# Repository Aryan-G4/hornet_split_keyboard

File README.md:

# Hornet Keyboard — Split Wireless Communication and Charging Mechanical Keyboard PCB

The Hornet Keyboard is the *first* fully custom, split, mechanical keyboard featuring integrated **Bluetooth**, **Qi wireless charging** on either split, and optional **USB-C programmability/Connectivity**.  
This project represents a complete end-to-end embedded hardware design — from schematic capture to multi-layer PCB layout — optimized for both performance and manufacturability.

---

## Project Overview

| Feature | Description |
|----------|-------------|
| **Form Factor** | Compact Split ergonomic layout key matrix |
| **Microcontroller** | Industry standard NRF52840 QIAA semi-BGA |
| **MCU Interface** | USB-C (DFU bootloader + HID communication) and STLinkV3 SWD |
| **Wireless** | On-board Bluetooth LE trace antenna with matched RF trace and controlled impedance |
| **Power** | Dual power paths: 3.7 V LiPo battery or USB VBUS (5 V) with power switching (USB PRIORITY)|
| **Charging Options** | USB-C Power Delivery (5V @ 1000mA) or Qi wireless charging receiver (5V @ 800mA)|
| **Firmware** | DFU-based update over USB; designed for ZMK and QMK-style firmware structure |
| **Sensors** | On-board voltage monitoring and NTC-based battery temperature protection |
| **Other** | Rotary encoders, Jumpers to probe and enable/disable submodules | standardized M3 mounting holes |
---
## Schematics

## Layout

3D model (ish)

Individual Layers:
L1: FCu

L2: In1

L3: In2

L4: BCu

## System Architecture

The system integrates three major electrical domains:

1. **Digital Domain (nRF52840)**
   - Industry standard MCU with built-in BLE 5.4
   - High-speed interrupt-based matrix scanning and battery management.
   - Dedicated power pin for reading battery charge.

2. **Power Management Domain**
   - Dual-source power path with **ideal diode OR-ing** between USB VBUS and LiPo battery.
   - **Li-Ion charge controller** managing both USB and Qi charge inputs.
   - **Dynamic load sharing** ensures stable operation while charging.
   - **Overcurrent and thermal protection** via FET-based switching and NTC feedback.

3. **Wireless RF Domain**
   - Custom-routed **50 Ω matched trace** for the Bluetooth antenna.
   - π-matching network for impedance tuning based on antenna manufacturer data.
   - Keepout and ground clearance zone designed per RF layout guidelines.

---

## Electrical Design Highlights

- **4-layer PCB** for clean separation of signal, power, and RF planes.
- **Differential USB data routing** (D+ / D–) with 90 Ω differential impedance.
- **Common-mode choke** and ESD suppression on USB-C connector for EMI resilience.
- **Reverse-current blocking MOSFET** for power path control between USB and battery.
- **Qi receiver integration** including rectification, voltage regulation, and charge negotiation.
- **Seamless transition** between wireless power and USB without brownout.

## Tools and Workflow

- **KiCad 8.0** — schematic capture and PCB design  
- **JLCPCB / LCSC** — fabrication and component sourcing  
- **SolidWorks** — mechanical fit and case alignment  
- **ZMK** - Open source repo for wireless split keyboards
- **DFU-util** — firmware flashing over USB-C and SWD through my STLinkV3

---

## Firmware Architecture 
- Utilize USBC's DFU to flash all firmware and STLinkV3 to flash in case of USBC fail
- Implement ZMK- wireless open source keyboard firmware kit for wireless split keyboards
- Implement QMK alternatively, for wired keyboards
- Eventually write my own firmware, optimizing speed and runtime.

---

---

## Gallery and work in progress photos :D

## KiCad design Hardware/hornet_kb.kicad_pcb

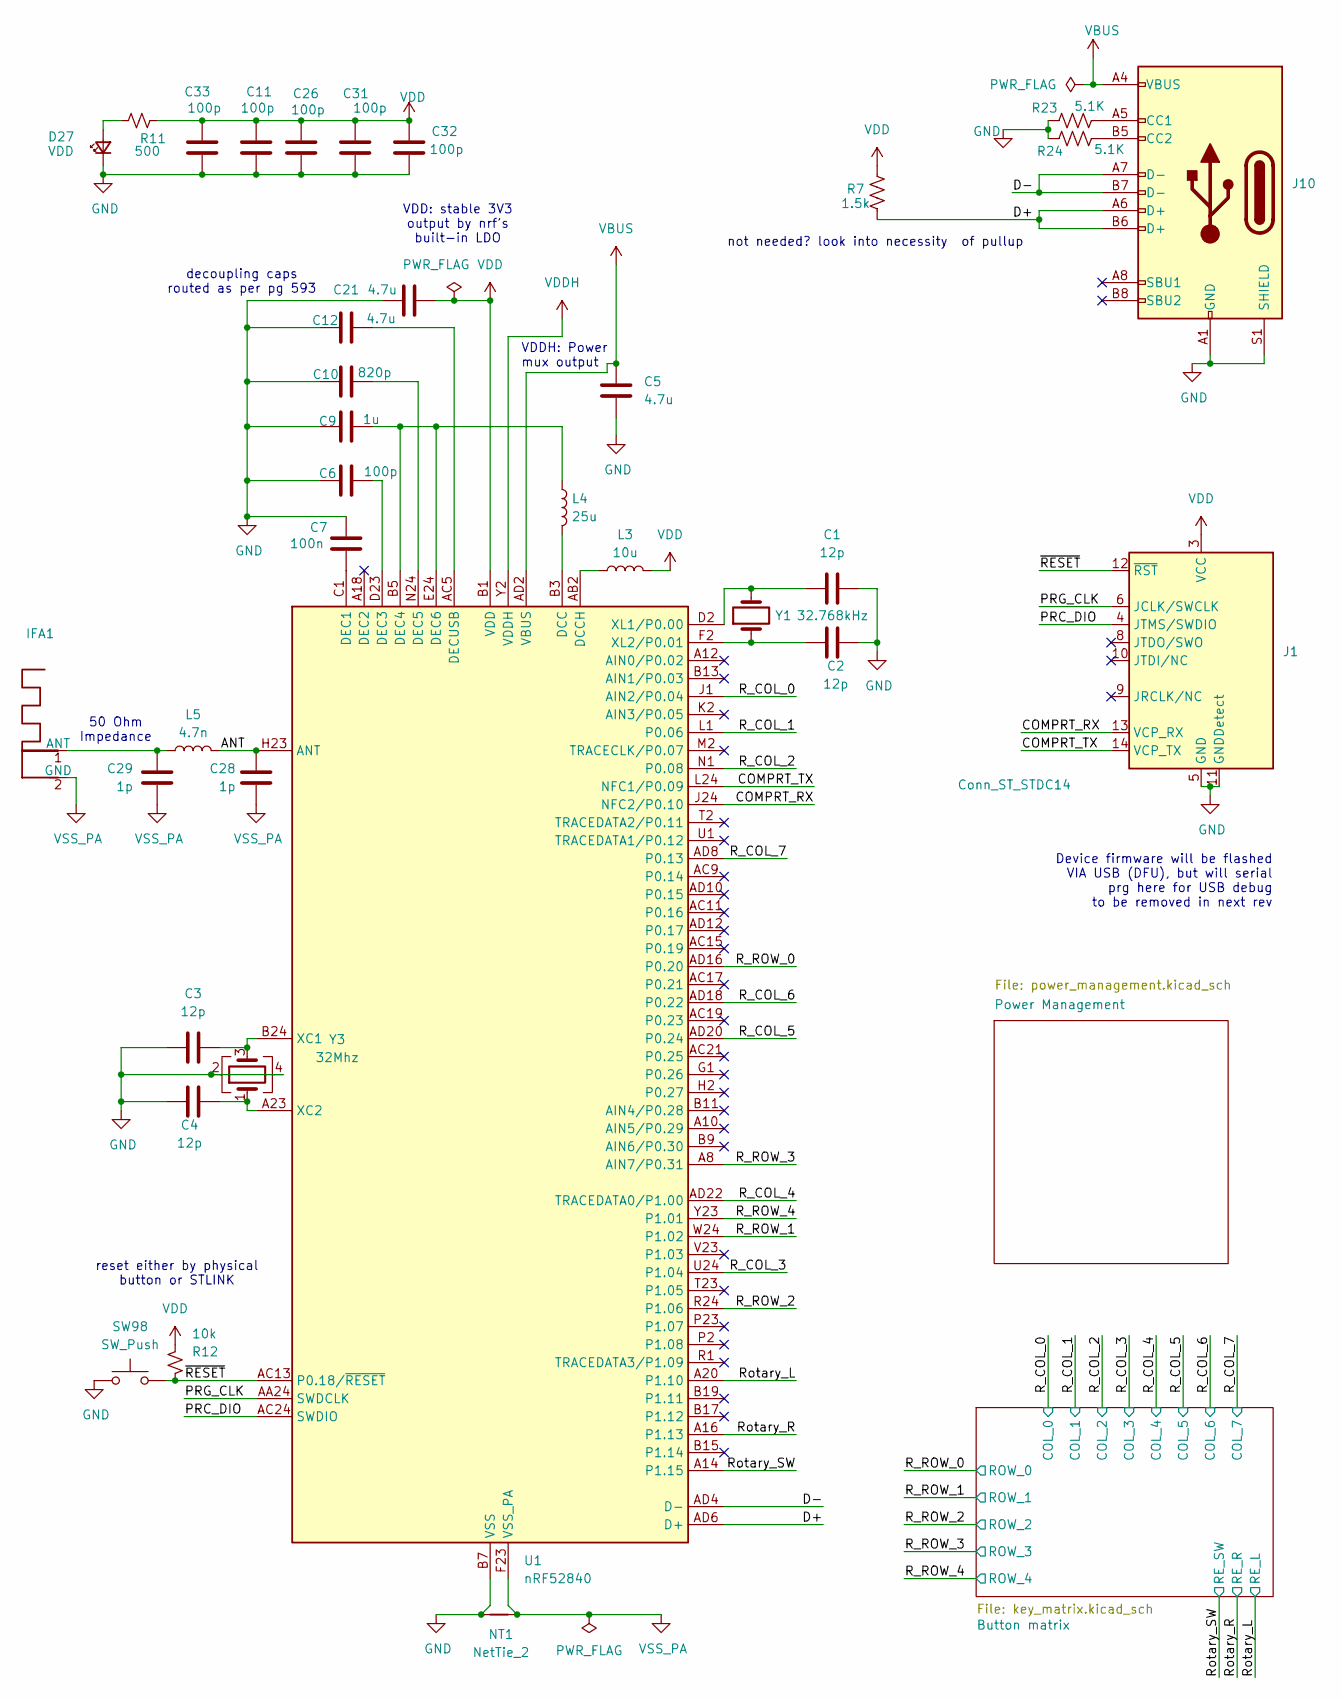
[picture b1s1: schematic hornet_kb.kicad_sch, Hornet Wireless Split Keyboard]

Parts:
C1, C2, C3, C4: 12p; C_0402_1005Metric; LCSC C1547
C5, C12, C21: 4.7u; C_0805_2012Metric; LCSC C1779
C6, C11, C26, C31, C32, C33: 100p; C_0603_1608Metric; LCSC C14858
C7: 100n; C_0603_1608Metric; LCSC C14663
C9: 1u; C_0603_1608Metric; LCSC C15849
C10: 820p; C_0603_1608Metric; LCSC C107057
C28, C29: 1p; C_0402_1005Metric; LCSC C1550
D27: VDD; LED_0402_1005Metric; LCSC C30584803
IFA1: Texas_SWRA117D_2.4GHz_Right
J1: Conn_ST_STDC14; Tag-Connect_TC2070-IDC-FP_2x07_P1.27mm_Vertical
J10: USB_C_Receptacle_USB2.0; USB_C_Receptacle_HRO_TYPE-C-31-M-12; LCSC C165948
L3: 10u; L_0402_1005Metric; LCSC C436512
L4: 25u; L_0402_1005Metric; LCSC C12669
L5: 4.7n; L_0402_1005Metric; LCSC C86065
NT1: NetTie_2; NetTie-2_SMD_Pad2.0mm
R7: 1.5k; R_0603_1608Metric; LCSC C22843
R11: 500; R_0603_1608Metric; LCSC C6207671
R12: 10k; R_0603_1608Metric; LCSC C25804
R23, R24: 5.1K; R_0603_1608Metric; LCSC C23186
SW98: SW_Push; SW_DIP_SPSTx01_Slide_6.7x4.1mm_W6.73mm_P2.54mm_LowProfile_J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; LCSC C720477
U1: nRF52840; Nordic_AQFN-73-1EP_7x7mm_P0.5mm; LCSC C190794
Y1: 32.768kHz; Crystal_SMD_3215-2Pin_3.2x1.5mm; LCSC C32346
Y3: 32Mhz; Crystal_SMD_2016-4Pin_2.0x1.6mm; LCSC C5339095

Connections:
/ANT: C28.1, L5.1, U1.H23 (ANT)
/COMPRT_RX: J1.13 (VCP_RX), U1.J24 (NFC2/P0.10)
/COMPRT_TX: J1.14 (VCP_TX), U1.L24 (NFC1/P0.09)
/D+: J10.A6 (D+), J10.B6 (D+), R7.2, U1.AD6 (D+)
/D-: J10.A7 (D-), J10.B7 (D-), U1.AD4 (D-)
/PRC_DIO: J1.4 (JTMS/SWDIO), U1.AC24 (SWDIO)
/PRG_CLK: J1.6 (JCLK/SWCLK), U1.AA24 (SWDCLK)
/R_COL_0: U1.J1 (AIN2/P0.04); also elsewhere on the board
/R_COL_1: U1.L1 (P0.06); also elsewhere on the board
/R_COL_2: U1.N1 (P0.08); also elsewhere on the board
/R_COL_3: U1.U24 (P1.04); also elsewhere on the board
/R_COL_4: U1.AD22 (TRACEDATA0/P1.00); also elsewhere on the board
/R_COL_5: U1.AD20 (P0.24); also elsewhere on the board
/R_COL_6: U1.AD18 (P0.22); also elsewhere on the board
/R_COL_7: U1.AD8 (P0.13); also elsewhere on the board
/R_ROW_0: U1.AD16 (P0.20); also elsewhere on the board
/R_ROW_1: U1.W24 (P1.02); also elsewhere on the board
/R_ROW_2: U1.R24 (P1.06); also elsewhere on the board
/R_ROW_3: U1.A8 (AIN7/P0.31); also elsewhere on the board
/R_ROW_4: U1.Y23 (P1.01); also elsewhere on the board
/Rotary_L: U1.A20 (P1.10); also elsewhere on the board
/Rotary_R: U1.A16 (P1.13); also elsewhere on the board
/Rotary_SW: U1.A14 (P1.15); also elsewhere on the board
/~RESET: J1.12 (~RST), R12.2, SW98.1, U1.AC13 (P0.18/~RESET)
GND: C1.1, C2.1, C3.1, C4.1, C5.2, C6.2, C7.2, C9.2, C10.1, C11.2, C12.2, C21.1, C26.2, C31.2, C32.2, C33.2, D27.1 (K), J1.5 (GND), J1.7 (GND), J1.11 (GNDDetect), J10.A1 (GND), J10.A12 (GND), J10.B1 (GND), J10.B12 (GND), J10.S1 (SHIELD), NT1.2, R23.1, R24.1, SW98.2, U1.B7 (VSS), U1.EP (VSS), Y3.2, Y3.4; also elsewhere on the board
unnamed: D27.2 (A), R11.2
unnamed: C29.1, IFA1.1 (ANT), L5.2
unnamed: J10.A5 (CC1), R23.2
unnamed: J10.B5 (CC2), R24.2
unnamed: L4.1, U1.B3 (DCC)
unnamed: L3.2, U1.AB2 (DCCH)
unnamed: C7.1, U1.C1 (DEC1)
unnamed: C6.1, U1.D23 (DEC3)
unnamed: C9.1, L4.2, U1.B5 (DEC4), U1.E24 (DEC6)
unnamed: C10.2, U1.N24 (DEC5)
unnamed: C12.1, U1.AC5 (DECUSB)
unnamed: C3.2, U1.B24 (XC1), Y3.3
unnamed: C4.2, U1.A23 (XC2), Y3.1
unnamed: C1.2, U1.D2 (XL1/P0.00), Y1.2
unnamed: C2.2, U1.F2 (XL2/P0.01), Y1.1
VBUS: C5.1, J10.A4 (VBUS), J10.A9 (VBUS), J10.B4 (VBUS), J10.B9 (VBUS), U1.AD2 (VBUS); also elsewhere on the board
VDD: C11.1, C21.2, C26.1, C31.1, C32.1, C33.1, J1.3 (VCC), L3.1, R7.1, R11.1, R12.1, U1.A22 (VDD), U1.AD14 (VDD), U1.AD23 (VDD), U1.B1 (VDD), U1.W1 (VDD); also elsewhere on the board
VDDH: U1.Y2 (VDDH); also elsewhere on the board
VSS_PA: C28.2, C29.2, IFA1.2 (GND), NT1.1, U1.F23 (VSS_PA)

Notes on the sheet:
VDDH: Power mux output
50 Ohm Impedance
Device firmware will be flashed VIA USB (DFU), but will serial prg here for USB debug to be removed in next rev
decoupling caps routed as per pg 593
VDD: stable 3V3 output by nrf's built-in LDO
reset either by physical button or STLINK
not needed? look into necessity of pullup

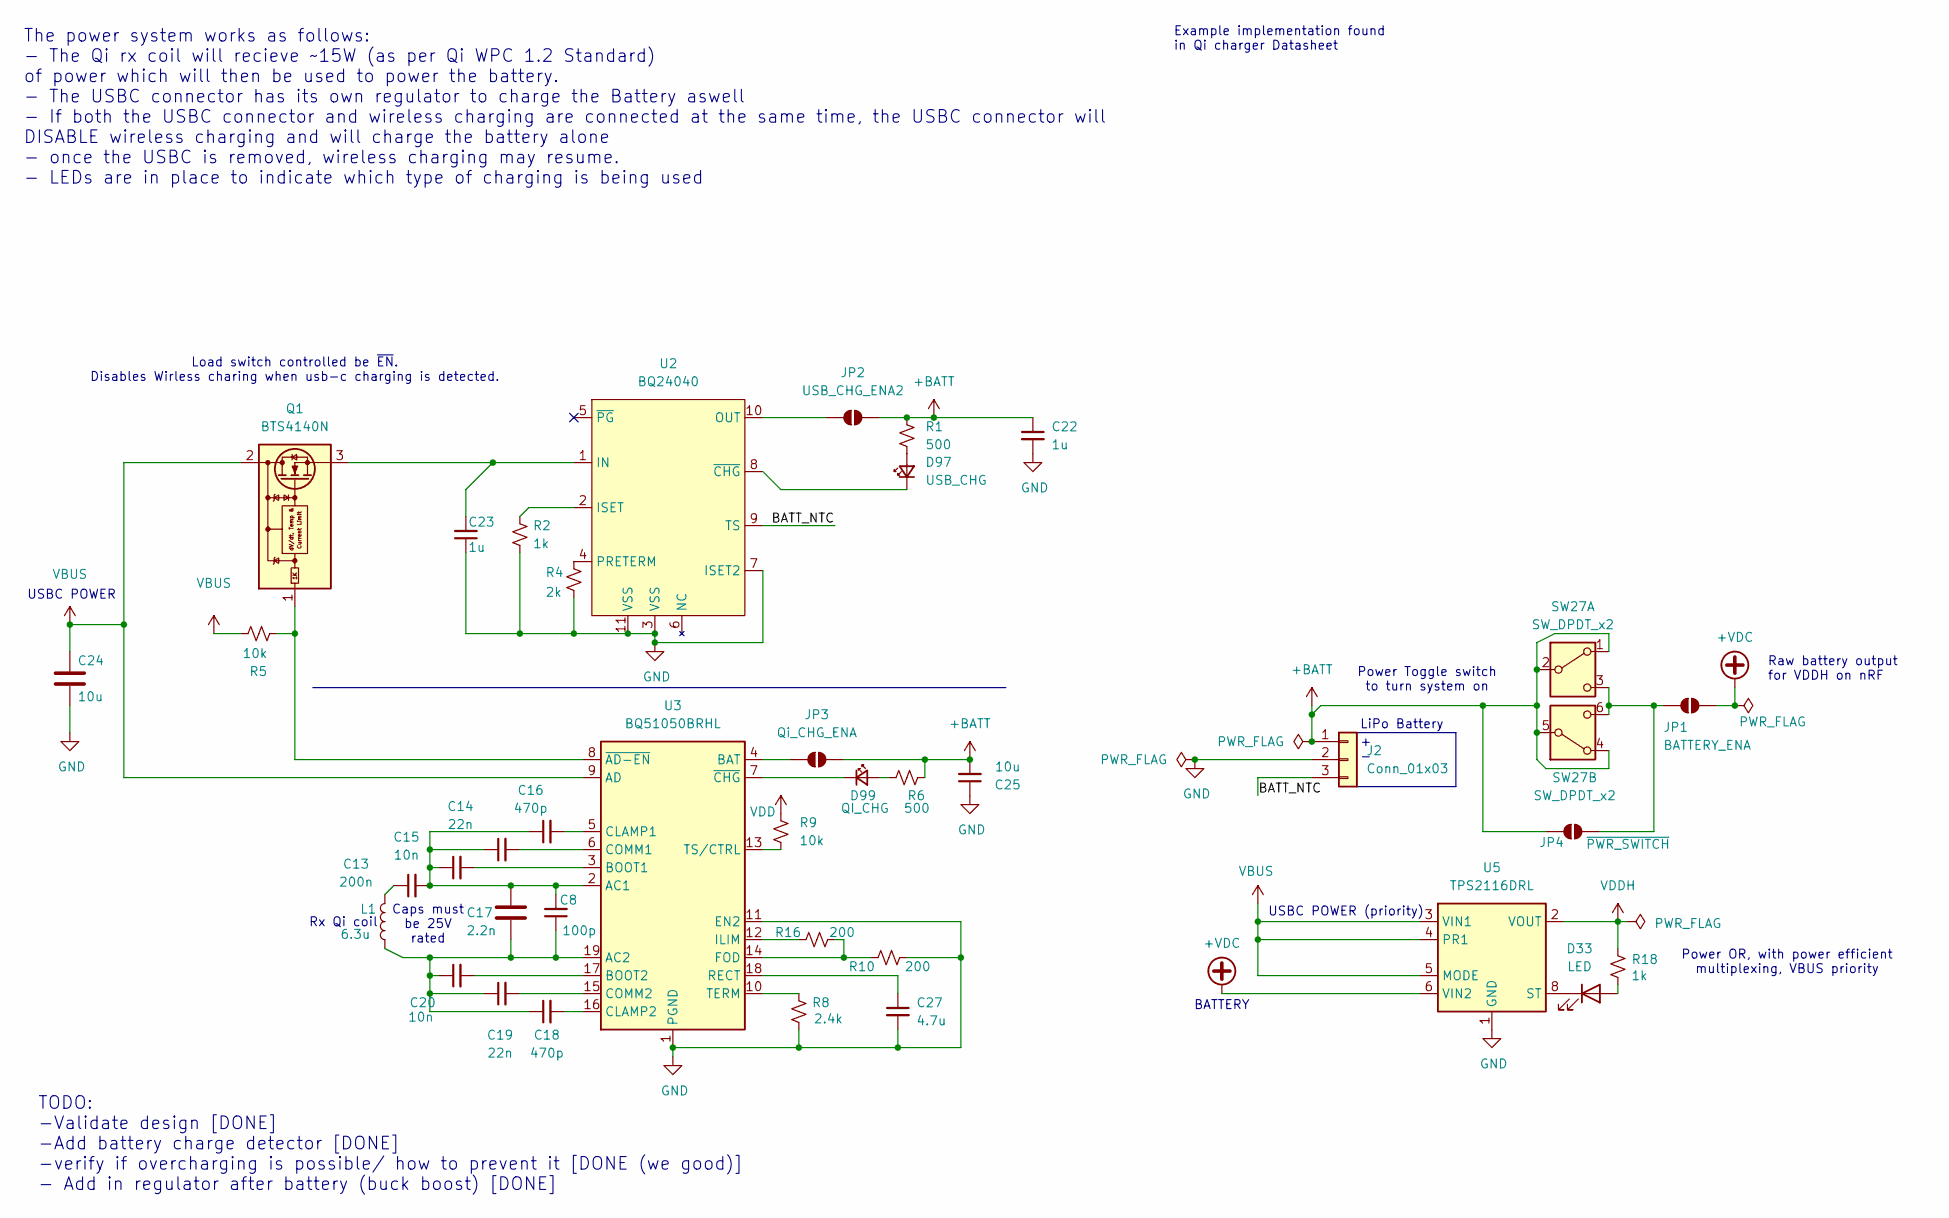
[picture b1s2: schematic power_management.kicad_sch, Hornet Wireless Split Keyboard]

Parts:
C8: 100p; C_0603_1608Metric; LCSC C14858
C13: 200n; C_0603_1608Metric; LCSC C1002
C14, C19: 22n; C_0603_1608Metric; LCSC C21122
C15, C20: 10n; C_0603_1608Metric; LCSC C57112
C16, C18: 470p; C_0603_1608Metric; LCSC C1620
C17: 2.2n; C_0603_1608Metric; LCSC C1604
C22, C23: 1u; C_0603_1608Metric; LCSC C15849
C24, C25: 10u; C_0603_1608Metric; LCSC C19702
C27: 4.7u; C_0603_1608Metric; LCSC C19666
D33: LED; LED_0402_1005Metric; LCSC C28310436
D97: USB_CHG; LED_0402_1005Metric; LCSC C20608784
D99: QI_CHG; LED_0402_1005Metric; LCSC C20608784
J2: Conn_01x03; JST_GH_SM03B-GHS-TB_1x03-1MP_P1.25mm_Horizontal; LCSC C514175
JP1: BATTERY_ENA; SolderJumper-2_P1.3mm_Open_TrianglePad1.0x1.5mm
JP2: USB_CHG_ENA2; SolderJumper-2_P1.3mm_Open_TrianglePad1.0x1.5mm
JP3: Qi_CHG_ENA; SolderJumper-2_P1.3mm_Open_TrianglePad1.0x1.5mm
JP4: ~{PWR_SWITCH}; SolderJumper-2_P1.3mm_Open_TrianglePad1.0x1.5mm
L1: 6.3u; TerminalBlock_Phoenix_MKDS-1,5-2-5.08_1x02_P5.08mm_Horizont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; LCSC C8465
Q1: BTS4140N; SOT-223; LCSC C59442
R1, R6: 500; R_0603_1608Metric; LCSC C6207671
R2, R18: 1k; R_0603_1608Metric; LCSC C21190
R4: 2k; R_0603_1608Metric; LCSC C22975
R5, R9: 10k; R_0603_1608Metric; LCSC C25804
R8: 2.4k; R_0603_1608Metric; LCSC C22940
R10, R16: 200; R_0603_1608Metric; LCSC C8218
SW27: SW_DPDT_x2; SW_CK_JS202011CQN_DPDT_Straight; LCSC C1788494
U2: BQ24040; Texas_DLH0010A_WSON-10-1EP_2.2x2mm_P0.4mm_EP0.9x1.5mm_Therm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; LCSC C2876332
U3: BQ51050BRHL; Texas_VQFN-RHL-20; LCSC C133307
U5: TPS2116DRL; SOT-583-8; LCSC C3235557

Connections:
+BATT: C22.1, C25.2, J2.1, JP2.2 (B), JP3.2 (B), JP4.1 (A), R1.1, R6.1, SW27.1 (A), SW27.2 (B), SW27.4 (A), SW27.5 (B)
+VDC: JP1.2 (B), U5.6 (VIN2)
/Power Management/BATT_NTC: J2.3, U2.9 (TS)
GND: C22.2, C23.1, C24.2, C25.1, C27.2, J2.2, R2.1, R4.1, R8.2, R10.2, U2.3 (VSS), U2.7 (ISET2), U2.11 (VSS), U3.1 (PGND), U3.11 (EN2), U3.20 (PGND), U3.21 (PGND), U5.1 (GND); also elsewhere on the board
unnamed: C13.1, L1.2
unnamed: D33.2 (A), R18.1
unnamed: D33.1 (K), U5.8 (ST)
unnamed: D97.2 (A), R1.2
unnamed: D97.1 (K), U2.8 (~CHG)
unnamed: D99.2 (A), R6.2
unnamed: D99.1 (K), U3.7 (~CHG)
unnamed: JP1.1 (A), JP4.2 (B), SW27.3 (C), SW27.6 (C)
unnamed: JP2.1 (A), U2.10 (OUT)
unnamed: JP3.1 (A), U3.4 (BAT)
unnamed: Q1.1 (IN), R5.1, U3.8 (~AD-EN)
unnamed: C23.2, Q1.3 (OUT), U2.1 (IN)
unnamed: R2.2, U2.2 (ISET)
unnamed: R4.2, U2.4 (PRETERM)
unnamed: C8.2, C13.2, C14.1, C15.1, C16.1, C17.1, U3.2 (AC1)
unnamed: C8.1, C17.2, C18.1, C19.1, C20.1, L1.1, U3.19 (AC2)
unnamed: C15.2, U3.3 (BOOT1)
unnamed: C20.2, U3.17 (BOOT2)
unnamed: C16.2, U3.5 (CLAMP1)
unnamed: C18.2, U3.16 (CLAMP2)
unnamed: C14.2, U3.6 (COMM1)
unnamed: C19.2, U3.15 (COMM2)
unnamed: R10.1, R16.2, U3.14 (FOD)
unnamed: R16.1, U3.12 (ILIM)
unnamed: C27.1, U3.18 (RECT)
unnamed: R8.1, U3.10 (TERM)
unnamed: R9.2, U3.13 (TS/CTRL)
VBUS: C24.1, Q1.2 (V_{bb}), Q1.4 (V_{bb}), R5.2, U3.9 (AD), U5.3 (VIN1), U5.4 (PR1), U5.5 (MODE); also elsewhere on the board
VDD: R9.1; also elsewhere on the board
VDDH: R18.2, U5.2 (VOUT), U5.7 (VOUT); also elsewhere on the board

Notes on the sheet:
Power OR, with power efficient multiplexing, VBUS priority
Rx Qi coil
The power system works as follows: - The Qi rx coil will recieve ~15W (as per Qi WPC 1.2 Standard) of power which will then be used to power the battery. - The USBC connector has its own regulator to charge the Battery aswell - If both the USBC connector and wireless charging are connected at the s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
Raw battery output for VDDH on nRF
USBC POWER (priority)
USBC POWER
LiPo Battery
Example implementation found in Qi charger Datasheet
BATTERY
Caps must be 25V rated
Load switch controlled be ~{EN}. Disables Wirless charing when usb-c charging is detected.
Power Toggle switch to turn system on
+ -
TODO: -Validate design [DONE] -Add battery charge detector [DONE] -verify if overcharging is possible/ how to prevent it [DONE (we good)] - Add in regulator after battery (buck boost) [DONE]

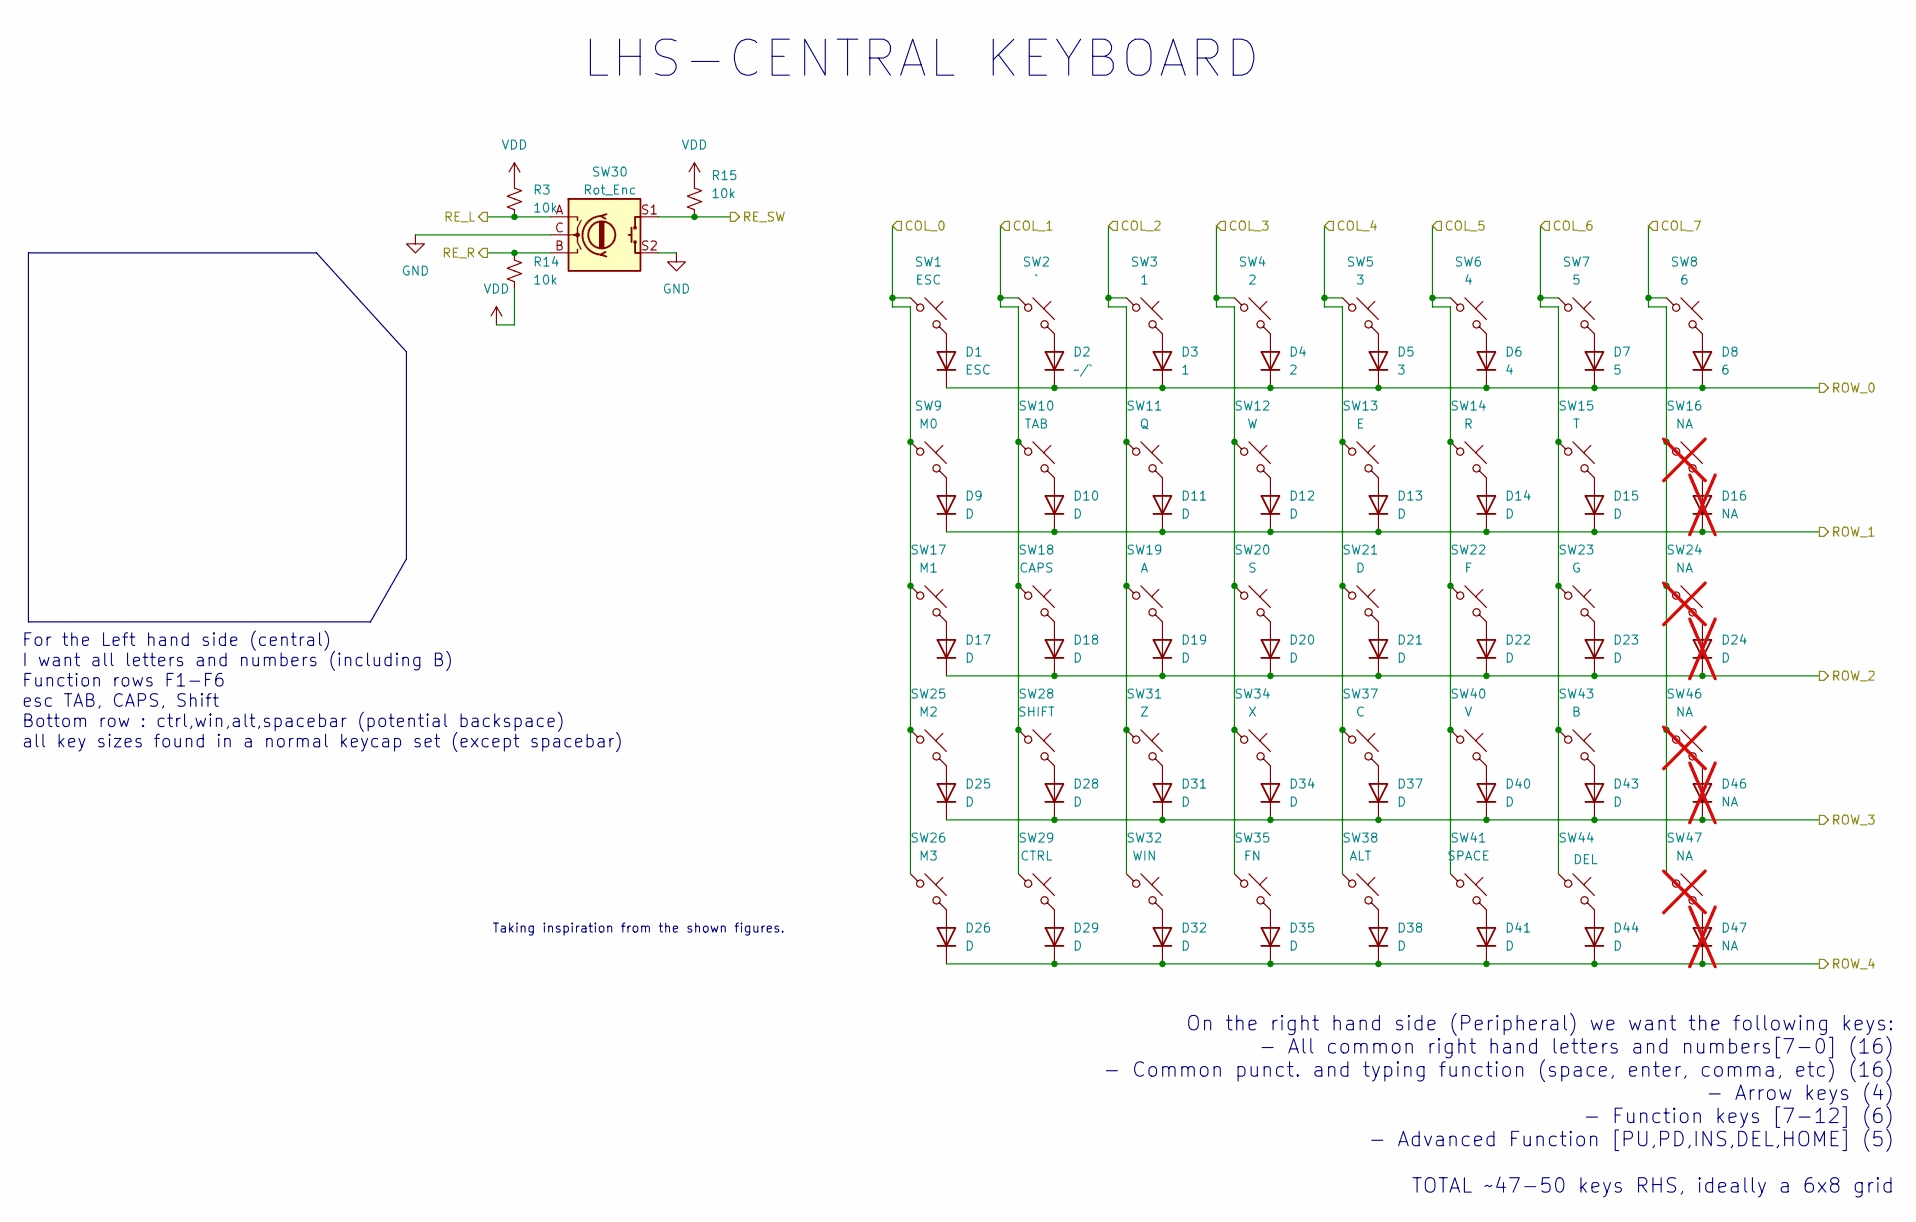
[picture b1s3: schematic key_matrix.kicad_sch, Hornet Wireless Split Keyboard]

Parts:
D1: ESC; Diode_SOD-123; LCSC C917030
D2: ~/`; Diode_SOD-123; LCSC C917030
D3: 1; Diode_SOD-123; LCSC C917030
D4: 2; Diode_SOD-123; LCSC C917030
D5: 3; Diode_SOD-123; LCSC C917030
D6: 4; Diode_SOD-123; LCSC C917030
D7: 5; Diode_SOD-123; LCSC C917030
D8: 6; Diode_SOD-123; LCSC C917030
D9, D10, D11, D12, D13, D14, D15, D17, D18, D19, D20, D21, D22, D23, D25, D26, D28, D29, D31, D32, D34, D35, D37, D38, D40, D41, D43, D44: D; Diode_SOD-123; LCSC C917030
D16, D46, D47: NA; Diode_SOD-123; not fitted
D24: D; Diode_SOD-123; not fitted
R3, R14, R15: 10k; R_0603_1608Metric; LCSC C25804
SW1: ESC; Hotswap_MX_1.00u; LCSC C41430893
SW2: `; Hotswap_MX_1.00u; LCSC C41430893
SW3: 1; Hotswap_MX_1.00u; LCSC C41430893
SW4: 2; Hotswap_MX_1.00u; LCSC C41430893
SW5: 3; Hotswap_MX_1.00u; LCSC C41430893
SW6: 4; Hotswap_MX_1.00u; LCSC C41430893
SW7: 5; Hotswap_MX_1.00u; LCSC C41430893
SW8: 6; Hotswap_MX_1.00u; LCSC C41430893
SW9: M0; Hotswap_MX_1.00u; LCSC C41430893
SW10: TAB; Hotswap_MX_1.50u; LCSC C41430893
SW11: Q; Hotswap_MX_1.00u; LCSC C41430893
SW12: W; Hotswap_MX_1.00u; LCSC C41430893
SW13: E; Hotswap_MX_1.00u; LCSC C41430893
SW14: R; Hotswap_MX_1.00u; LCSC C41430893
SW15: T; Hotswap_MX_1.00u; LCSC C41430893
SW16: NA; Hotswap_MX_1.00u; not fitted
SW17: M1; Hotswap_MX_1.00u; LCSC C41430893
SW18: CAPS; Hotswap_MX_1.75u; LCSC C41430893
SW19: A; Hotswap_MX_1.00u; LCSC C41430893
SW20: S; Hotswap_MX_1.00u; LCSC C41430893
SW21: D; Hotswap_MX_1.00u; LCSC C41430893
SW22: F; Hotswap_MX_1.00u; LCSC C41430893
SW23: G; Hotswap_MX_1.00u; LCSC C41430893
SW24: NA; Hotswap_MX_1.50u; not fitted
SW25: M2; Hotswap_MX_1.00u; LCSC C41430893
SW26: M3; Hotswap_MX_1.00u; LCSC C41430893
SW28: SHIFT; Hotswap_MX_2.25u; LCSC C41430893
SW29: CTRL; Hotswap_MX_1.25u; LCSC C41430893
SW30: Rot_Enc; RotaryEncoder_Alps_EC11E-Switch_Vertical_H20mm; LCSC C41430893
SW31: Z; Hotswap_MX_1.00u; LCSC C41430893
SW32: WIN; Hotswap_MX_1.00u; LCSC C41430893
SW34: X; Hotswap_MX_1.00u; LCSC C41430893
SW35: FN; Hotswap_MX_1.25u; LCSC C41430893
SW37: C; Hotswap_MX_1.00u; LCSC C41430893
SW38: ALT; Hotswap_MX_1.25u; LCSC C41430893
SW40: V; Hotswap_MX_1.00u; LCSC C41430893
SW41: SPACE; Hotswap_MX_2.25u; LCSC C41430893
SW43: B; Hotswap_MX_1.00u; LCSC C41430893
SW44: DEL; Hotswap_MX_1.00u; LCSC C41430893
SW46, SW47: NA; not fitted

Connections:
/R_COL_0: SW1.1, SW9.1, SW17.1, SW25.1, SW26.1; also elsewhere on the board
/R_COL_1: SW2.1, SW10.1, SW18.1, SW28.1, SW29.1; also elsewhere on the board
/R_COL_2: SW3.1, SW11.1, SW19.1, SW31.1, SW32.1; also elsewhere on the board
/R_COL_3: SW4.1, SW12.1, SW20.1, SW34.1, SW35.1; also elsewhere on the board
/R_COL_4: SW5.1, SW13.1, SW21.1, SW37.1, SW38.1; also elsewhere on the board
/R_COL_5: SW6.1, SW14.1, SW22.1, SW40.1, SW41.1; also elsewhere on the board
/R_COL_6: SW7.1, SW15.1, SW23.1, SW43.1, SW44.1; also elsewhere on the board
/R_COL_7: SW8.1, SW16.1, SW24.1, SW46.1, SW47.1; also elsewhere on the board
/R_ROW_0: D1.1 (K), D2.1 (K), D3.1 (K), D4.1 (K), D5.1 (K), D6.1 (K), D7.1 (K), D8.1 (K); also elsewhere on the board
/R_ROW_1: D9.1 (K), D10.1 (K), D11.1 (K), D12.1 (K), D13.1 (K), D14.1 (K), D15.1 (K), D16.1 (K); also elsewhere on the board
/R_ROW_2: D17.1 (K), D18.1 (K), D19.1 (K), D20.1 (K), D21.1 (K), D22.1 (K), D23.1 (K), D24.1 (K); also elsewhere on the board
/R_ROW_3: D25.1 (K), D28.1 (K), D31.1 (K), D34.1 (K), D37.1 (K), D40.1 (K), D43.1 (K), D46.1 (K); also elsewhere on the board
/R_ROW_4: D26.1 (K), D29.1 (K), D32.1 (K), D35.1 (K), D38.1 (K), D41.1 (K), D44.1 (K), D47.1 (K); also elsewhere on the board
/Rotary_L: R3.1, SW30.A; also elsewhere on the board
/Rotary_R: R14.2, SW30.B; also elsewhere on the board
/Rotary_SW: R15.1, SW30.S1; also elsewhere on the board
GND: SW30.C, SW30.S2; also elsewhere on the board
unnamed: D1.2 (A), SW1.2
unnamed: D2.2 (A), SW2.2
unnamed: D3.2 (A), SW3.2
unnamed: D4.2 (A), SW4.2
unnamed: D5.2 (A), SW5.2
unnamed: D6.2 (A), SW6.2
unnamed: D7.2 (A), SW7.2
unnamed: D8.2 (A), SW8.2
unnamed: D9.2 (A), SW9.2
unnamed: D10.2 (A), SW10.2
unnamed: D11.2 (A), SW11.2
unnamed: D12.2 (A), SW12.2
unnamed: D13.2 (A), SW13.2
unnamed: D14.2 (A), SW14.2
unnamed: D15.2 (A), SW15.2
unnamed: D16.2 (A), SW16.2
unnamed: D17.2 (A), SW17.2
unnamed: D18.2 (A), SW18.2
unnamed: D19.2 (A), SW19.2
unnamed: D20.2 (A), SW20.2
unnamed: D21.2 (A), SW21.2
unnamed: D22.2 (A), SW22.2
unnamed: D23.2 (A), SW23.2
unnamed: D24.2 (A), SW24.2
unnamed: D25.2 (A), SW25.2
unnamed: D26.2 (A), SW26.2
unnamed: D28.2 (A), SW28.2
unnamed: D29.2 (A), SW29.2
unnamed: D31.2 (A), SW31.2
unnamed: D32.2 (A), SW32.2
unnamed: D34.2 (A), SW34.2
unnamed: D35.2 (A), SW35.2
unnamed: D37.2 (A), SW37.2
unnamed: D38.2 (A), SW38.2
unnamed: D40.2 (A), SW40.2
unnamed: D41.2 (A), SW41.2
unnamed: D43.2 (A), SW43.2
unnamed: D44.2 (A), SW44.2
unnamed: D46.2 (A), SW46.2
unnamed: D47.2 (A), SW47.2
VDD: R3.2, R14.1, R15.2; also elsewhere on the board

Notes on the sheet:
For the Left hand side (central) I want all letters and numbers (including B) Function rows F1-F6 esc TAB, CAPS, Shift Bottom row : ctrl,win,alt,spacebar (potential backspace) all key sizes found in a normal keycap set (except spacebar)
On the right hand side (Peripheral) we want the following keys: - All common right hand letters and numbers[7-0] (16) - Common punct. and typing function (space, enter, comma, etc) (16) - Arrow keys (4) - Function keys [7-12] (6) - Advanced Function [PU,PD,INS,DEL,HOME] (5) TOTAL ~47-50 keys RHS, i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
LHS-CENTRAL KEYBOARD
Taking inspiration from the shown figures.

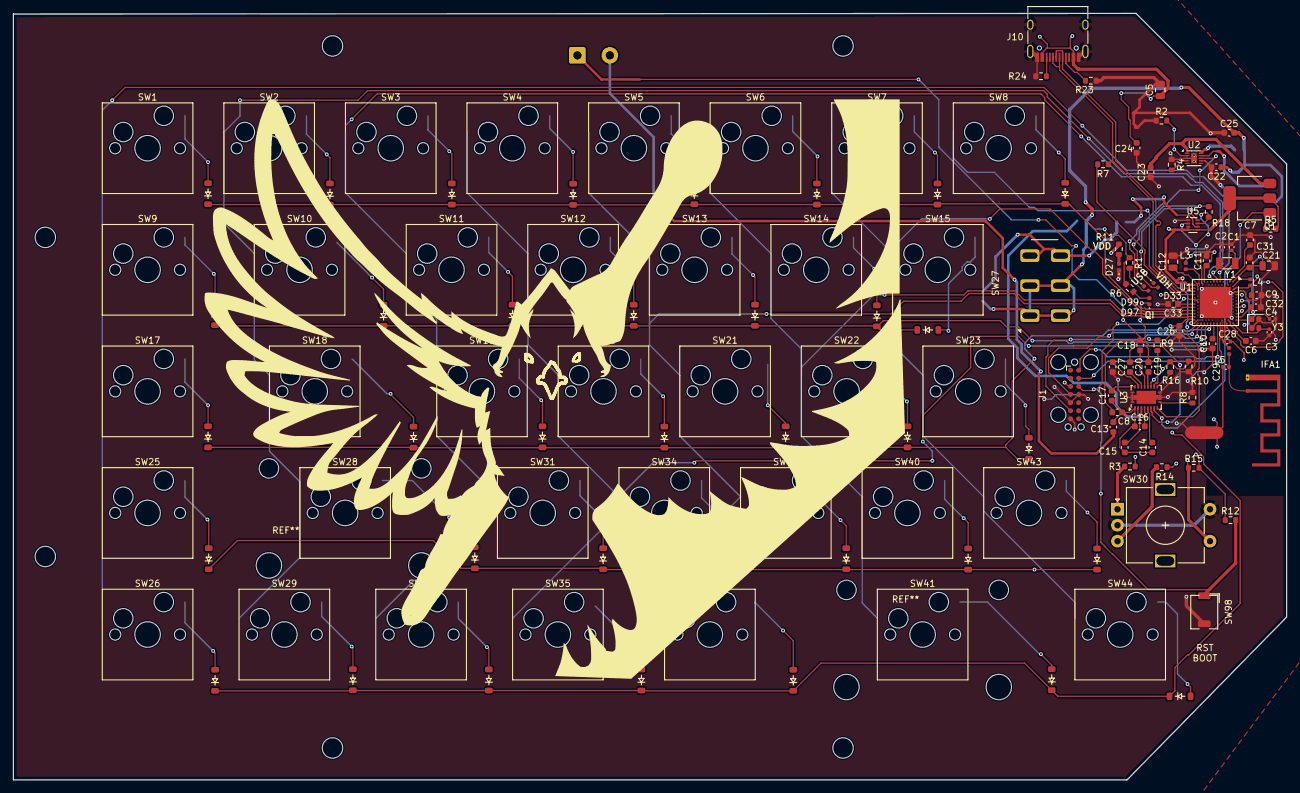
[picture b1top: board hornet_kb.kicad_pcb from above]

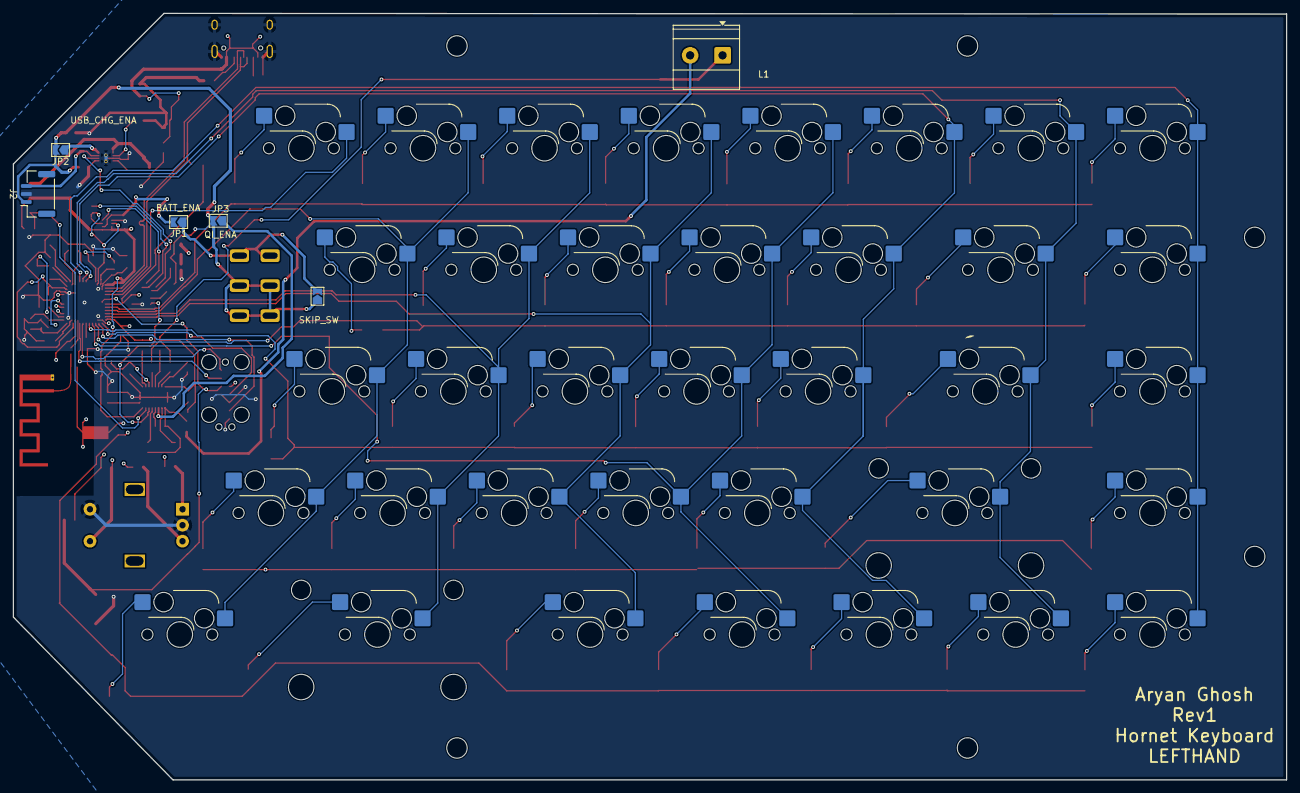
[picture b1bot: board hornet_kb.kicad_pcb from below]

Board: 4 copper layers, 199.5 x 120.1 mm, 149 parts (6 on the bottom side), 110 nets.

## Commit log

2025-10-25 Resolving DRC errors
2025-10-25 Change reset switchto custom footprint
2025-10-25 added mounting holes
2025-10-25 ADded cardinal
2025-10-26 Add LCSC part numbers and new resistor to PCB
    Added LCSC part numbers to multiple components in hornet_kb.kicad_pcb for improved BOM generation. Introduced a new 500Ω resistor (R11) and updated net assignments for Q1 and D27. Modified .gitignore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
2025-10-26 Added LCSC part defs
2025-10-26 Final Commits before production
2025-10-26 Revise README for Hornet Keyboard project
    Updated README to provide detailed project overview, features, schematics, layout, system architecture, design challenges, tools, firmware architecture, and key learning outcomes.
2025-10-26 Revise README with new content and images
    Updated README to include new images, firmware architecture details, and tools used. Removed design challenges section and added gallery section.
2025-11-03 Enhance description of Hornet Keyboard features
2025-11-07 Add image to Hornet Keyboard project README
    Added an image to the README for visual representation.
2025-11-07 Add mechanical files for case and plate
2025-11-08 Small adjustments
